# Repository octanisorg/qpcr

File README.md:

# Octanis qPCR

Quantitative PCR or sometimes called real-time PCR is a method to amplify a target DNA molecule and monitor its replication via fluorescence. The objective of this Octanis qPCR is to build a reliable and open qPCR machine for research purposes.

## COVID-19 and PCR

COVID-19 testing involves qPCR machines where an additional step needs to be completed prior to amplification. Using an enzyme called [Reverse Transcriptase](https://en.wikipedia.org/wiki/Reverse_transcriptase) the viral RNA is turned into DNA that the [Polymerase](https://en.wikipedia.org/wiki/Polymerase) can work with. 

## Current state

We are currently working on assembling the first PCBs and writing firmware. As we finalize the first prototype we will be updating this repository with our work in progress. 

If you are interested in contributing to the project [DM us](https://twitter.com/octanisorg). there are lots of cool sub-projects:
- STM32 firmware development
- SPICE simulation
- Case design
- Device GUI development

On our task list:
- Publication of an eBOM and mBOM.
- Collaboration with somebody making PCR tests/master mixes.
- Complete assembly as a STEP file. 

Completed:
- [Lid Heater PCB](https://pcb.im/share/dadb9a33574c403e)
- [16 Channel Excitation PCB](https://pcb.im/share/144b98556b9944f6)
- [8 Channel Emmision Sensing PCB](https://pcb.im/share/420ee10b3fee4fb8)
- [mainboard PCB](http://pcb.im/share/4b724f7b39da497d)

## Acknowledgements
- Chaibio, for the block and lid heater design, which we slightly modified.

## Sponsors
- [Octanis Instruments GmbH](https://www.octanis.ch) is helping with engineering and manufacturing.

## Similar projects
- [Chai Open qPCR](https://www.chaibio.com/openqpcr)
- [Ninja PCR](https://hackaday.io/project/174501-covid-19-detectors-300-real-time-pcr-50-lamp)

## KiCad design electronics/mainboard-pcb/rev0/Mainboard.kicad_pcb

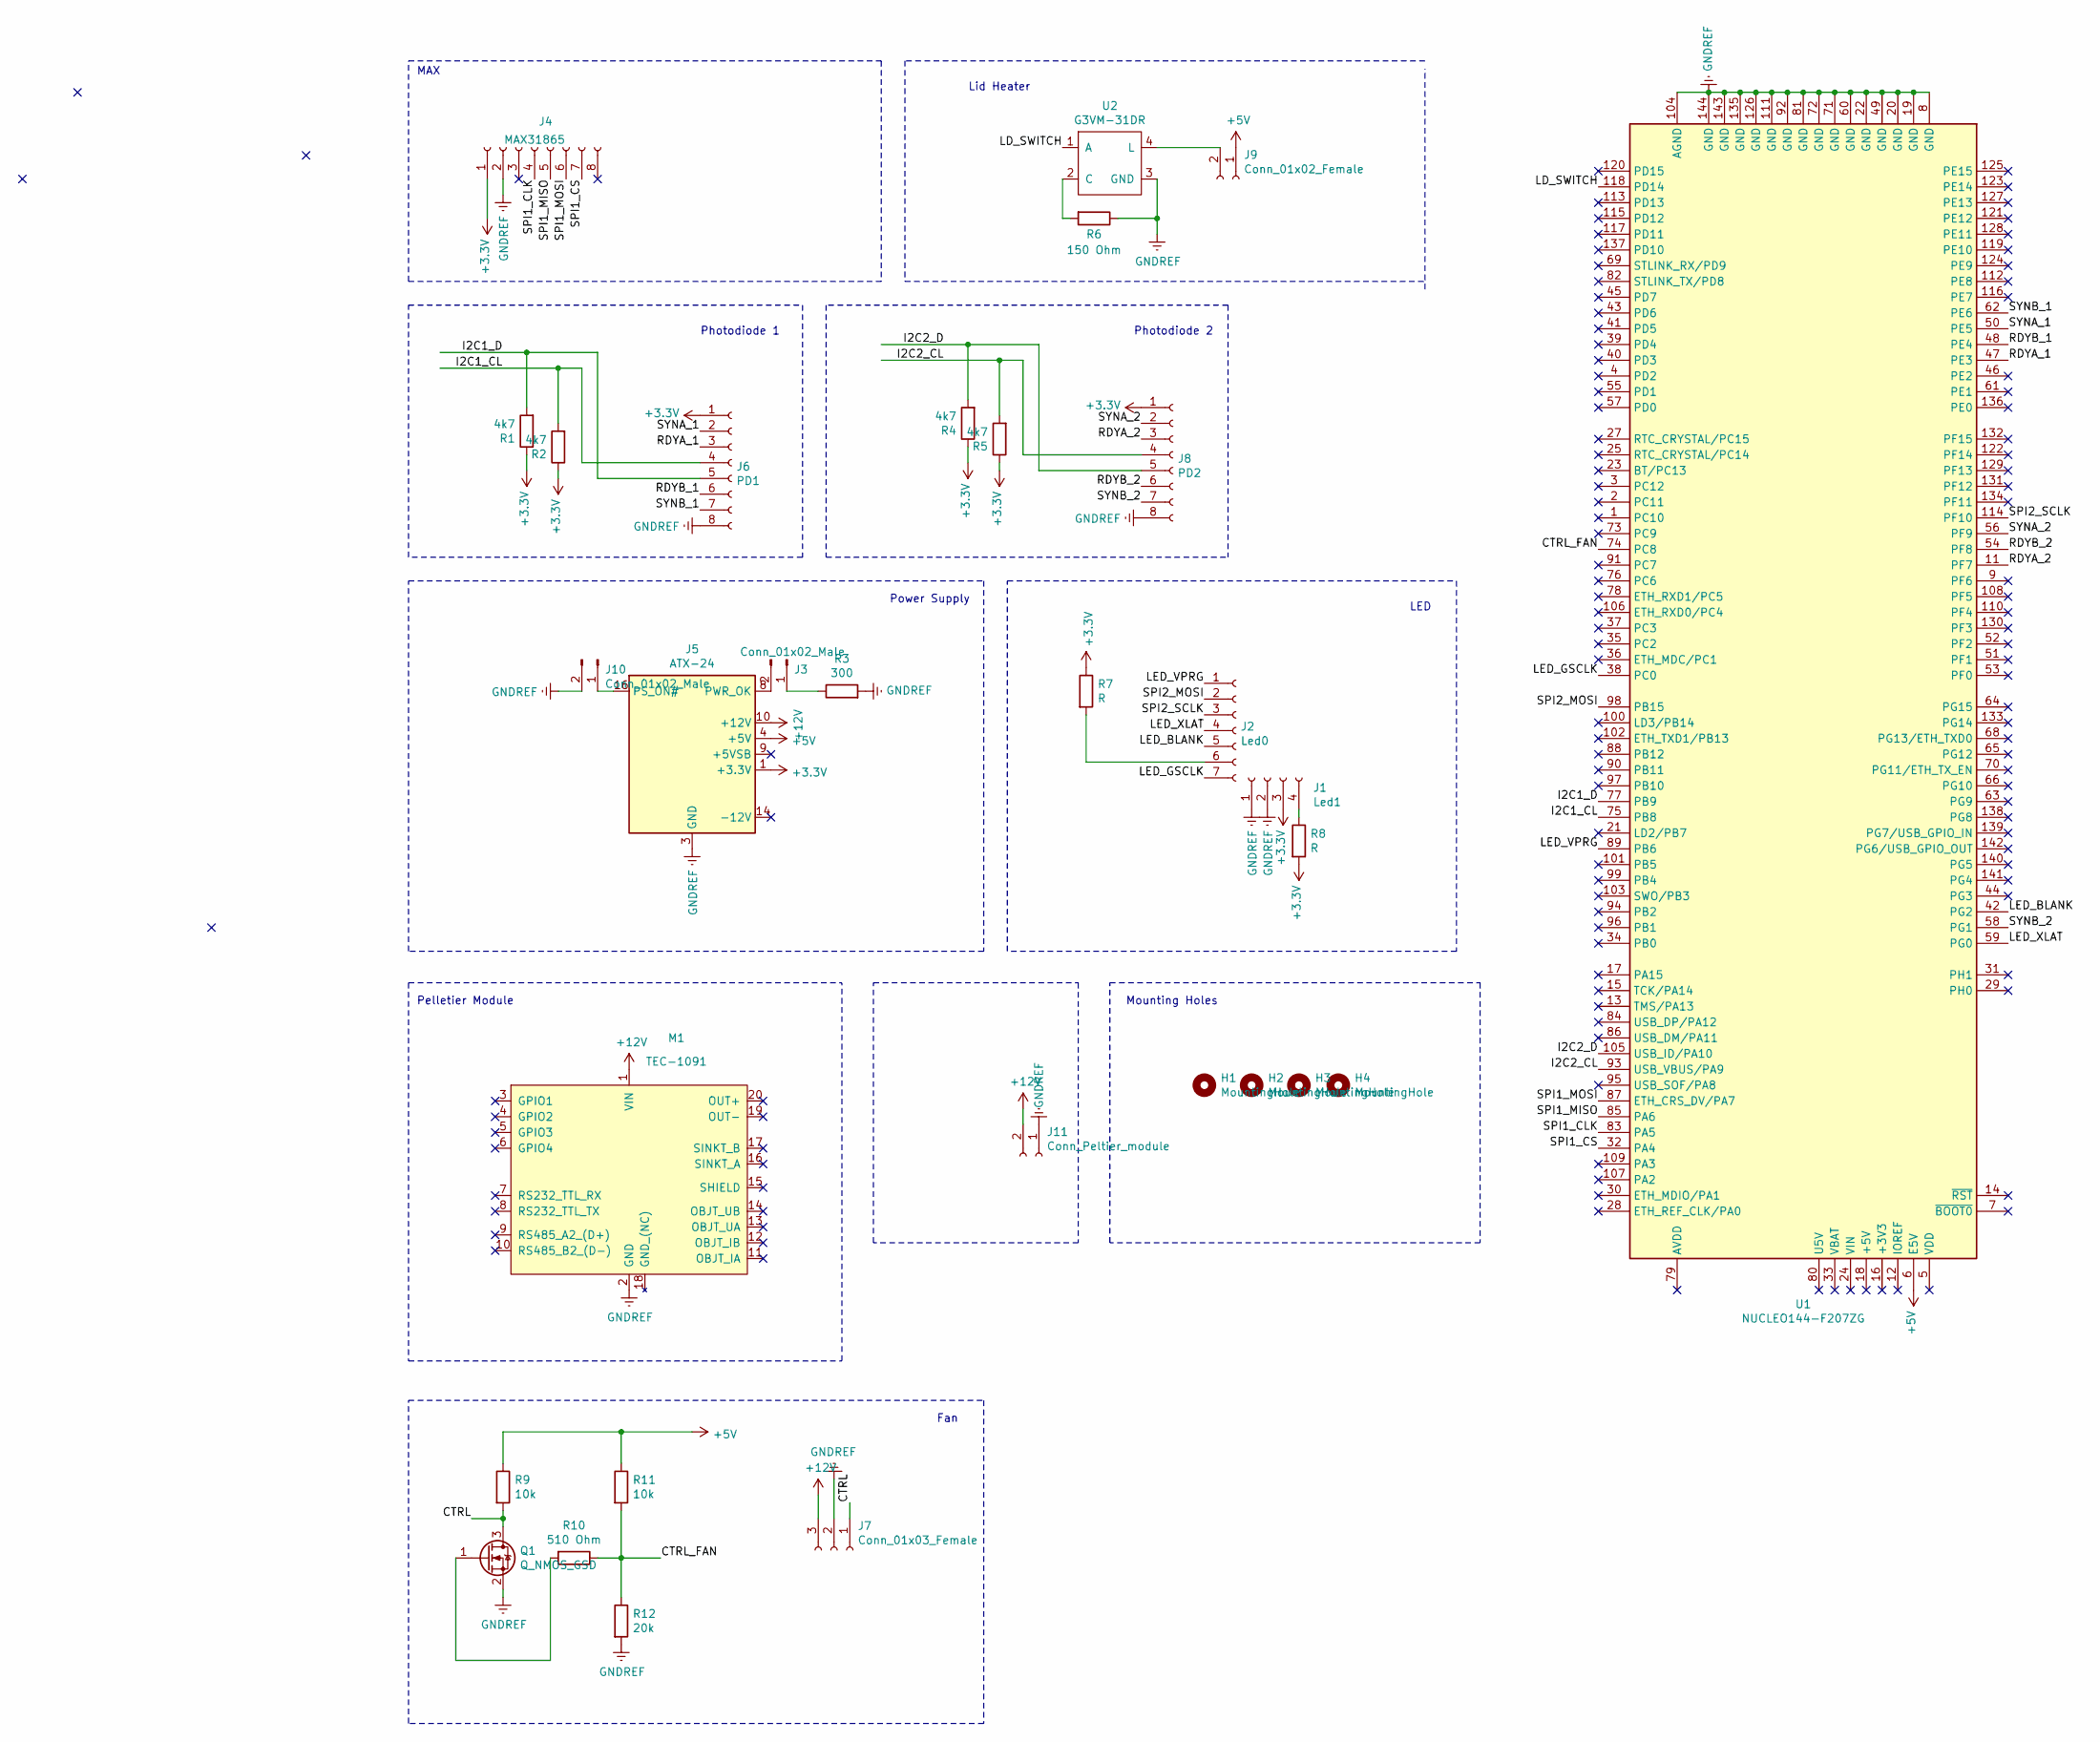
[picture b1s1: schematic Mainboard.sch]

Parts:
H1, H2, H3, H4: MountingHole; MountingHole_3.2mm_M3
J1: Led1; PinHeader_1x04_P2.54mm_Vertical
J2: Led0; PinHeader_1x07_P2.54mm_Vertical
J3, J10: Conn_01x02_Male; PinHeader_1x02_P2.54mm_Vertical
J4: MAX31865
J5: ATX-24; Molex_Mini-Fit_Jr_5569-24A1_2x12_P4.20mm_Horizontal; MPN 39291248
J6: PD1; PinHeader_1x08_P2.54mm_Vertical
J7: Conn_01x03_Female; PinHeader_1x03_P2.54mm_Vertical
J8: PD2; PinHeader_1x08_P2.54mm_Vertical
J9: Conn_01x02_Female; PinHeader_1x02_P2.54mm_Vertical
J11: Conn_Peltier_module; PinHeader_1x02_P2.54mm_Vertical
M1: TEC-1091; TEC-1091_alternate_pads; MPN TEC-1091
Q1: Q_NMOS_GSD; SOT-323_SC-70_Handsoldering; MPN SSM3K345R,LF
R1, R2, R4, R5: 4k7; R_0805_2012Metric_Pad1.15x1.40mm_HandSolder
R3: 300; R_0805_2012Metric_Pad1.15x1.40mm_HandSolde
R6: 150 Ohm; R_0805_2012Metric_Pad1.15x1.40mm_HandSolde
R7, R8: R; R_0805_2012Metric_Pad1.15x1.40mm_HandSolder
R9, R11: 10k; R_0805_2012Metric_Pad1.15x1.40mm_HandSolder
R10: 510 Ohm; R_0805_2012Metric_Pad1.15x1.40mm_HandSolder
R12: 20k; R_0805_2012Metric_Pad1.15x1.40mm_HandSolder
U1: NUCLEO144-F207ZG; ST_Morpho_Connector_144_STLink; MPN2 NUCLEO-F303ZE
U2: G3VM-31DR; MPN G3VM-31DR

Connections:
+3V3: J1.3, J4.1, J5.1 (+3.3V), J5.2 (+3.3V), J5.12 (+3.3V), J5.13 (+3.3V), J6.1, J8.1, R1.1, R2.1, R4.1, R5.1, R7.1, R8.2
+5V: J5.4 (+5V), J5.6 (+5V), J5.21 (+5V), J5.22 (+5V), J5.23 (+5V), J9.1, R9.1, R11.1, U1.6 (E5V)
+12V: J5.10 (+12V), J5.11 (+12V), J7.3, J11.2, M1.1 (VIN)
/CTRL: J7.1, Q1.3 (D), R9.2
/CTRL_FAN: R10.1, R11.2, R12.1, U1.74 (PC8)
/I2C1_CL: J6.4, R2.2, U1.75 (PB8)
/I2C1_D: J6.5, R1.2, U1.77 (PB9)
/I2C2_CL: J8.4, R5.2, U1.93 (USB_VBUS/PA9)
/I2C2_D: J8.5, R4.2, U1.105 (USB_ID/PA10)
/LD_SWITCH: U1.118 (PD14), U2.1 (A)
/LED_BLANK: J2.5, U1.42 (PG2)
/LED_GSCLK: J2.7, U1.38 (PC0)
/LED_VPRG: J2.1, U1.89 (PB6)
/LED_XLAT: J2.4, U1.59 (PG0)
/RDYA_1: J6.3, U1.47 (PE3)
/RDYA_2: J8.3, U1.11 (PF7)
/RDYB_1: J6.6, U1.48 (PE4)
/RDYB_2: J8.6, U1.54 (PF8)
/SPI1_CLK: J4.4, U1.83 (PA5)
/SPI1_CS: J4.7, U1.32 (PA4)
/SPI1_MISO: J4.5, U1.85 (PA6)
/SPI1_MOSI: J4.6, U1.87 (ETH_CRS_DV/PA7)
/SPI2_MOSI: J2.2, U1.98 (PB15)
/SPI2_SCLK: J2.3, U1.114 (PF10)
/SYNA_1: J6.2, U1.50 (PE5)
/SYNA_2: J8.2, U1.56 (PF9)
/SYNB_1: J6.7, U1.62 (PE6)
/SYNB_2: J8.7, U1.58 (PG1)
GNDREF: J1.1, J1.2, J4.2, J5.3 (GND), J5.5 (GND), J5.7 (GND), J5.15 (GND), J5.17 (GND), J5.18 (GND), J5.19 (GND), J5.24 (GND), J6.8, J7.2, J8.8, J10.2, J11.1, M1.2 (GND), Q1.2 (S), R3.2, R6.1, R12.2, U1.8 (GND), U1.19 (GND), U1.20 (GND), U1.22 (GND), U1.49 (GND), U1.60 (GND), U1.71 (GND), U1.72 (GND), U1.81 (GND), U1.92 (GND), U1.104 (AGND), U1.111 (GND), U1.126 (GND), U1.135 (GND), U1.143 (GND), U1.144 (GND), U2.3 (GND)
unnamed: J1.4, R8.1
unnamed: J2.6, R7.2
unnamed: J3.1, R3.1
unnamed: J3.2, J5.8 (PWR_OK)
unnamed: J9.2, U2.4 (L)
unnamed: J5.16 (PS_ON#), J10.1
unnamed: Q1.1 (G), R10.2
unnamed: R6.2, U2.2 (C)

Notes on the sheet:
Lid Heater
Power Supply
MAX
Photodiode 1
Photodiode 2
LED
Pelletier Module
Fan
Mounting Holes

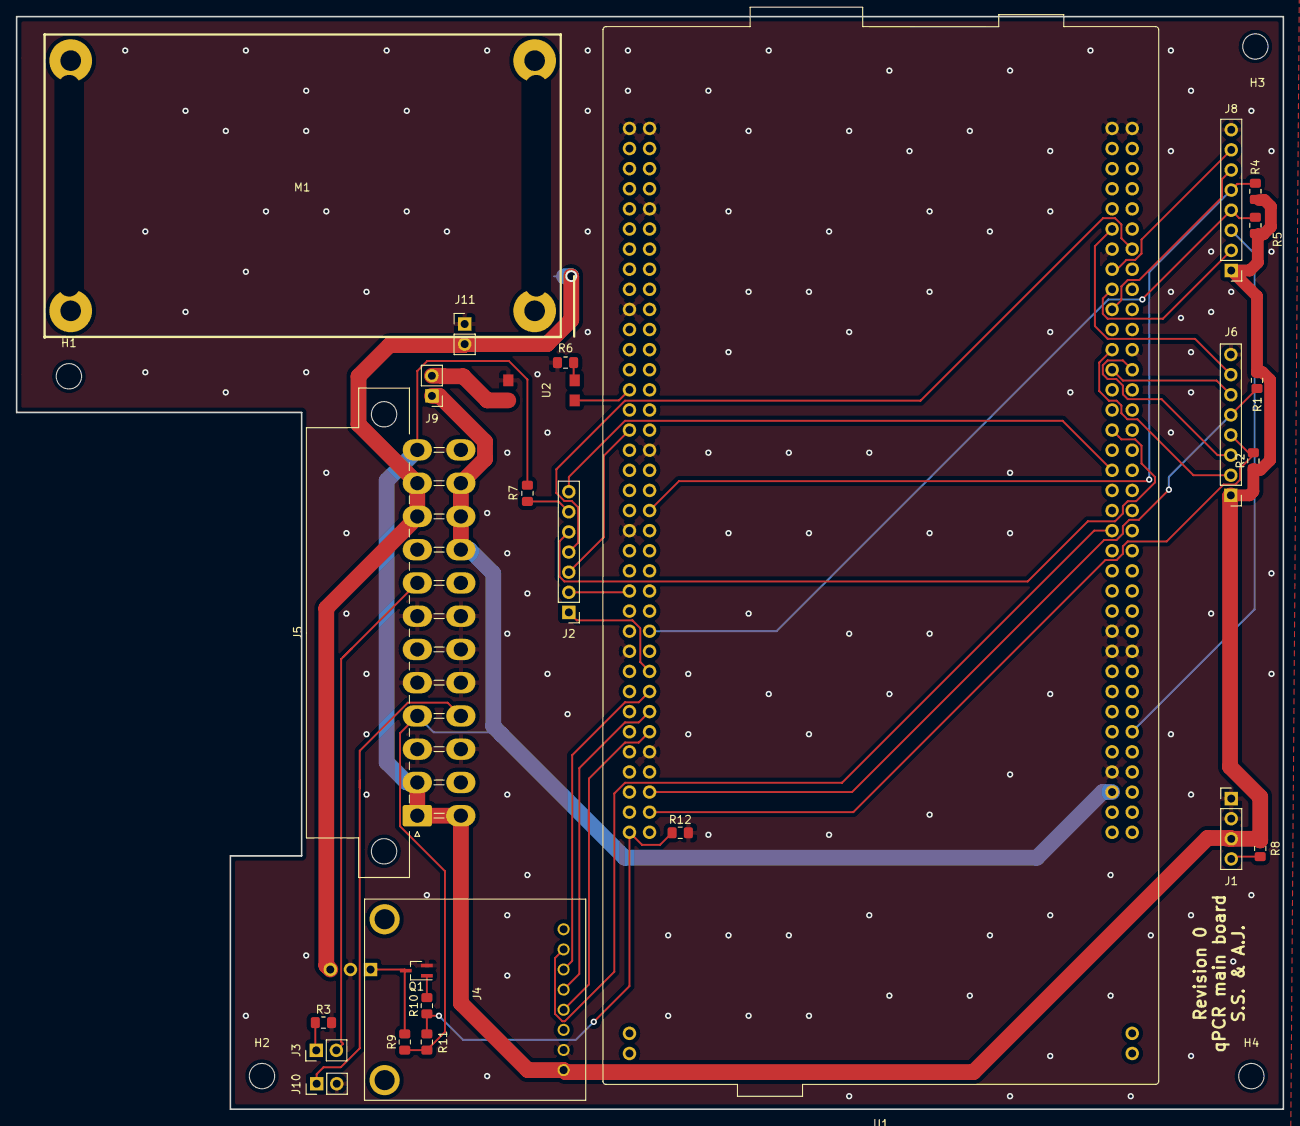
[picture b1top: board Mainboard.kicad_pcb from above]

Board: 2 copper layers, 160.0 x 138.0 mm, 31 parts (1 on the bottom side), 37 nets.

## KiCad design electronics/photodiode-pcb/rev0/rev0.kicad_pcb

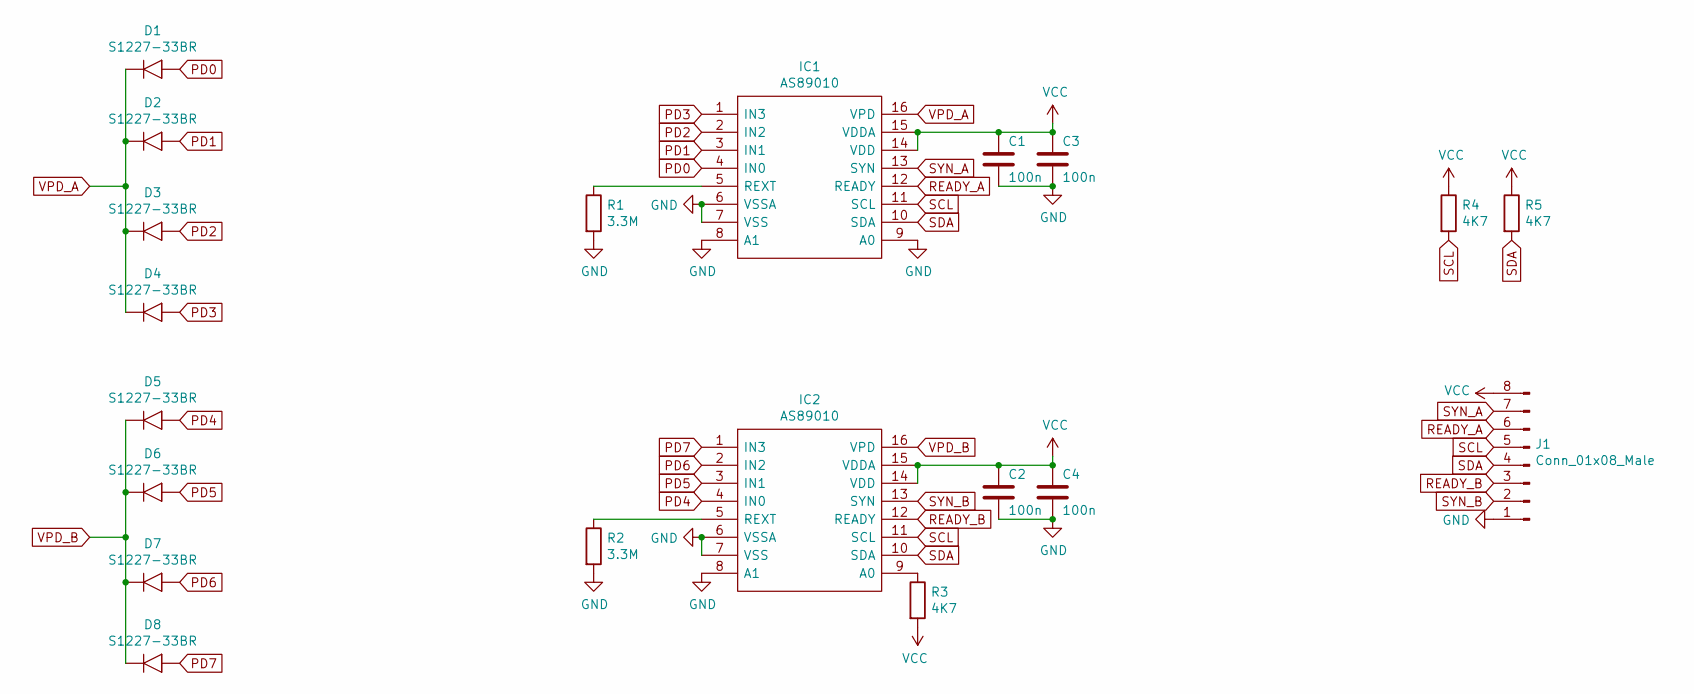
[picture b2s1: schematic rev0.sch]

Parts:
C1, C2, C3, C4: 100n; C_0402_1005Metric
D1, D2, D3, D4, D5, D6, D7, D8: S1227-33BR; MPN S1227-33BR
IC1, IC2: AS89010; SOP64P600X175-16N; Manufacturer_Part_Number AS89010; Mouser Part Number 985-AS89010
J1: Conn_01x08_Male; PinHeader_1x08_P1.00mm_Vertical
R1, R2: 3.3M; R_1206_3216Metric
R3, R4, R5: 4K7; R_0402_1005Metric

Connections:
GND: C1.2, C2.2, C3.2, C4.2, IC1.6 (VSSA), IC1.7 (VSS), IC1.8 (A1), IC1.9 (A0), IC2.6 (VSSA), IC2.7 (VSS), IC2.8 (A1), J1.1, R1.2, R2.2
unnamed: IC1.5 (REXT), R1.1
unnamed: IC2.5 (REXT), R2.1
unnamed: IC2.9 (A0), R3.1
PD0: D1.1, IC1.4 (IN0)
PD1: D2.1, IC1.3 (IN1)
PD2: D3.1, IC1.2 (IN2)
PD3: D4.1, IC1.1 (IN3)
PD4: D5.1, IC2.4 (IN0)
PD5: D6.1, IC2.3 (IN1)
PD6: D7.1, IC2.2 (IN2)
PD7: D8.1, IC2.1 (IN3)
READY_A: IC1.12 (READY), J1.6
READY_B: IC2.12 (READY), J1.3
SCL: IC1.11 (SCL), IC2.11 (SCL), J1.5, R4.2
SDA: IC1.10 (SDA), IC2.10 (SDA), J1.4, R5.2
SYN_A: IC1.13 (SYN), J1.7
SYN_B: IC2.13 (SYN), J1.2
VCC: C1.1, C2.1, C3.1, C4.1, IC1.14 (VDD), IC1.15 (VDDA), IC2.14 (VDD), IC2.15 (VDDA), J1.8, R3.2, R4.1, R5.1
VPD_A: D1.2, D2.2, D3.2, D4.2, IC1.16 (VPD)
VPD_B: D5.2, D6.2, D7.2, D8.2, IC2.16 (VPD)

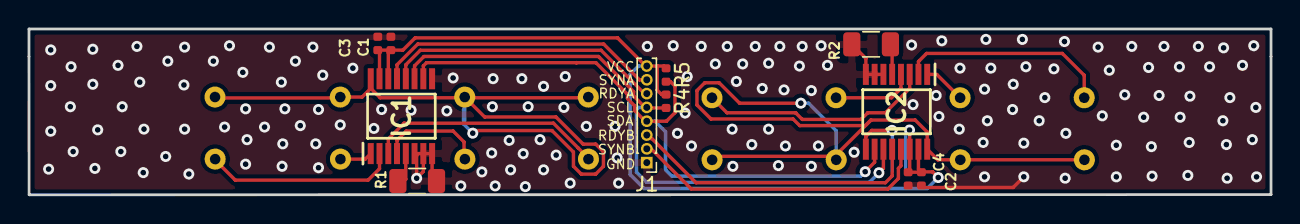
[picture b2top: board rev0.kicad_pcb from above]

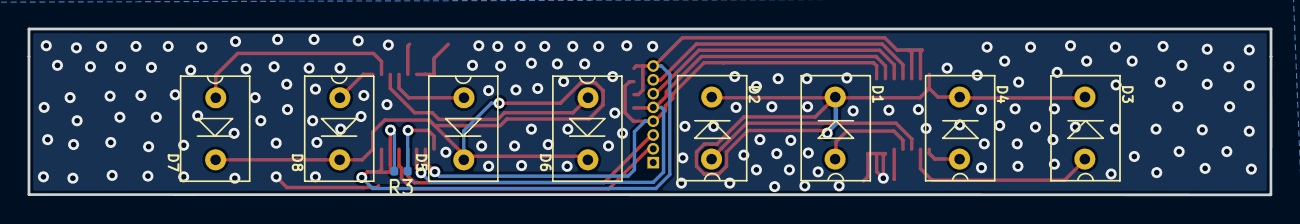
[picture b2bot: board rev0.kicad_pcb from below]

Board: 2 copper layers, 90.0 x 12.0 mm, 20 parts (9 on the bottom side), 21 nets.

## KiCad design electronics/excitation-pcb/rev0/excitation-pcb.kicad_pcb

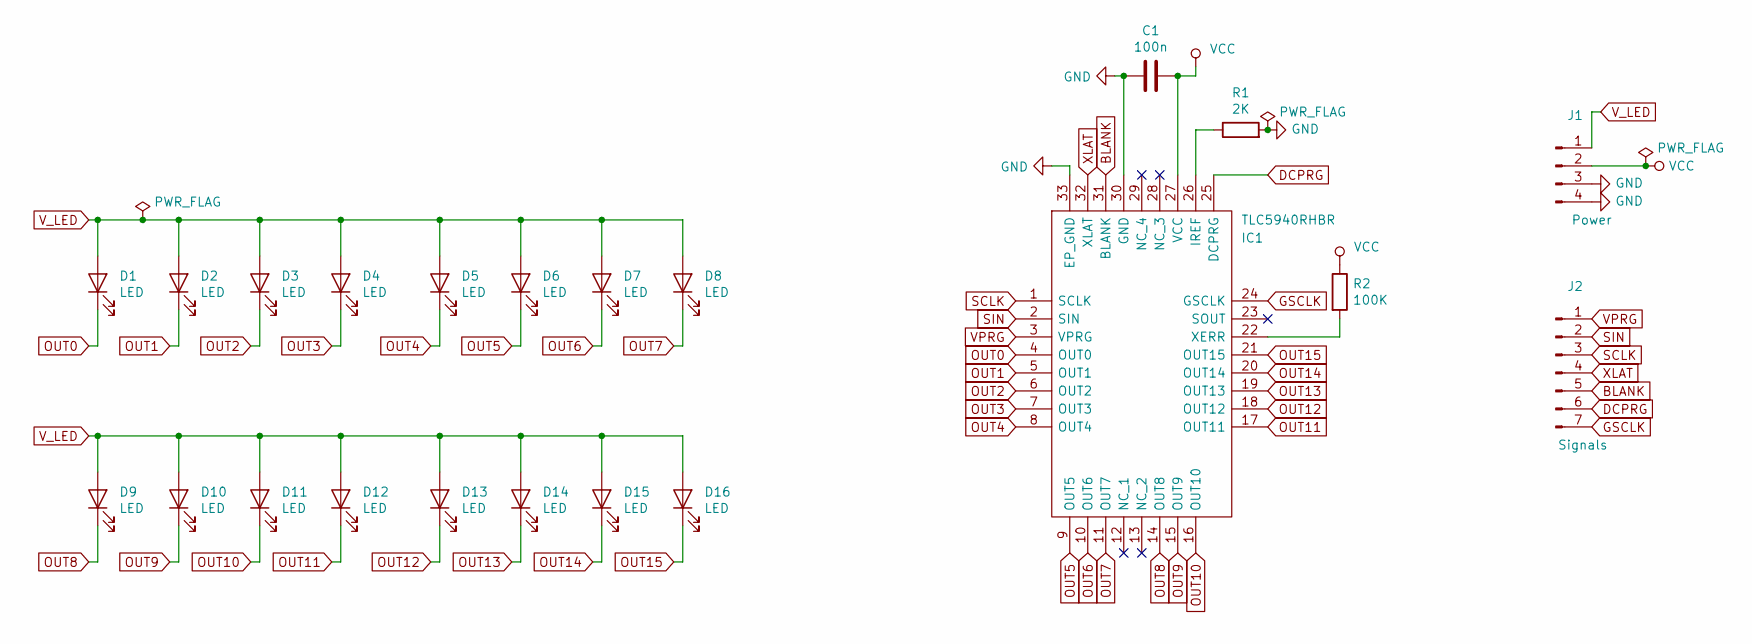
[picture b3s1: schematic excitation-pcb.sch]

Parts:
C1: 100n; C_0603_1608Metric
D1: LED; LED_D5.0mm; MPN C503B-BAS-CY0C0461
D2, D3, D4, D5, D6, D7, D8, D9, D10, D11, D12, D13, D14, D15, D16: LED; LED_D5.0mm
IC1: TLC5940RHBR; QFN50P500X500X100-33N-D; Manufacturer_Part_Number TLC5940RHBR; Mouser Part Number 595-TLC5940RHBR
J1: Power; PinHeader_1x04_P2.54mm_Vertical
J2: Signals; PinHeader_1x07_P2.54mm_Vertical
R1: 2K; R_0603_1608Metric
R2: 100K; R_0603_1608Metric

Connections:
BLANK: IC1.31 (BLANK), J2.5
DCPRG: IC1.25 (DCPRG), J2.6
GND: C1.2, IC1.30 (GND), IC1.33 (EP_GND), J1.3, J1.4, R1.2
GSCLK: IC1.24 (GSCLK), J2.7
unnamed: IC1.22 (XERR), R2.2
unnamed: IC1.26 (IREF), R1.1
OUT0: D1.1 (K), IC1.4 (OUT0)
OUT1: D2.1 (K), IC1.5 (OUT1)
OUT2: D3.1 (K), IC1.6 (OUT2)
OUT3: D4.1 (K), IC1.7 (OUT3)
OUT4: D5.1 (K), IC1.8 (OUT4)
OUT5: D6.1 (K), IC1.9 (OUT5)
OUT6: D7.1 (K), IC1.10 (OUT6)
OUT7: D8.1 (K), IC1.11 (OUT7)
OUT8: D9.1 (K), IC1.14 (OUT8)
OUT9: D10.1 (K), IC1.15 (OUT9)
OUT10: D11.1 (K), IC1.16 (OUT10)
OUT11: D12.1 (K), IC1.17 (OUT11)
OUT12: D13.1 (K), IC1.18 (OUT12)
OUT13: D14.1 (K), IC1.19 (OUT13)
OUT14: D15.1 (K), IC1.20 (OUT14)
OUT15: D16.1 (K), IC1.21 (OUT15)
SCLK: IC1.1 (SCLK), J2.3
SIN: IC1.2 (SIN), J2.2
VCC: C1.1, IC1.27 (VCC), J1.2, R2.1
VPRG: IC1.3 (VPRG), J2.1
V_LED: D1.2 (A), D2.2 (A), D3.2 (A), D4.2 (A), D5.2 (A), D6.2 (A), D7.2 (A), D8.2 (A), D9.2 (A), D10.2 (A), D11.2 (A), D12.2 (A), D13.2 (A), D14.2 (A), D15.2 (A), D16.2 (A), J1.1
XLAT: IC1.32 (XLAT), J2.4

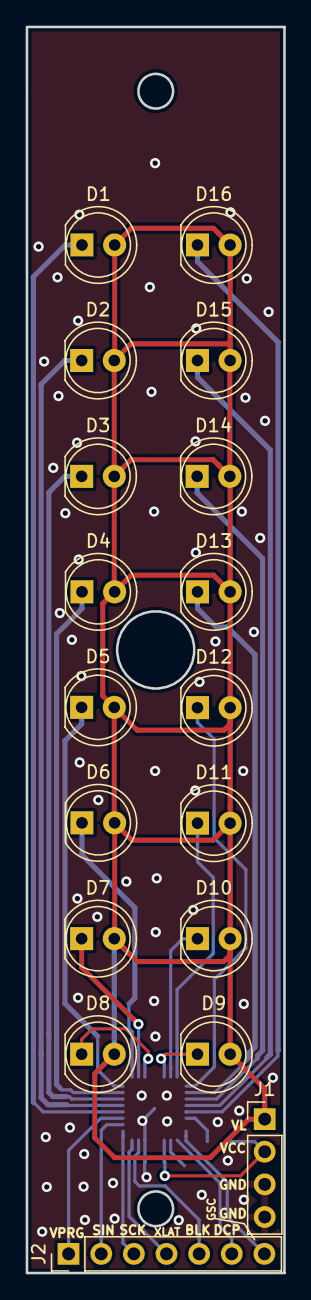
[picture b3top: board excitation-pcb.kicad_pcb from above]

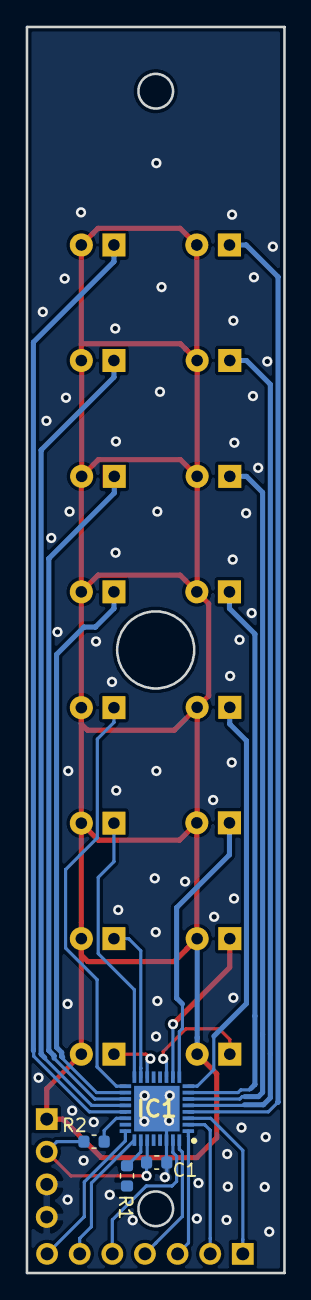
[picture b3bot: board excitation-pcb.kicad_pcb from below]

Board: 2 copper layers, 20.0 x 97.0 mm, 22 parts (4 on the bottom side), 28 nets.

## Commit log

2020-09-15 adding excitation, lidheater and photodiode pcbs from gitlab
2020-09-15 adding gitignore
2020-09-15 updating README. fixing edge_cuts in emmision pcb.
2020-09-15 updating gitignore
2020-09-15 adding mainboard PCB, updating README
2020-09-15 updating README
